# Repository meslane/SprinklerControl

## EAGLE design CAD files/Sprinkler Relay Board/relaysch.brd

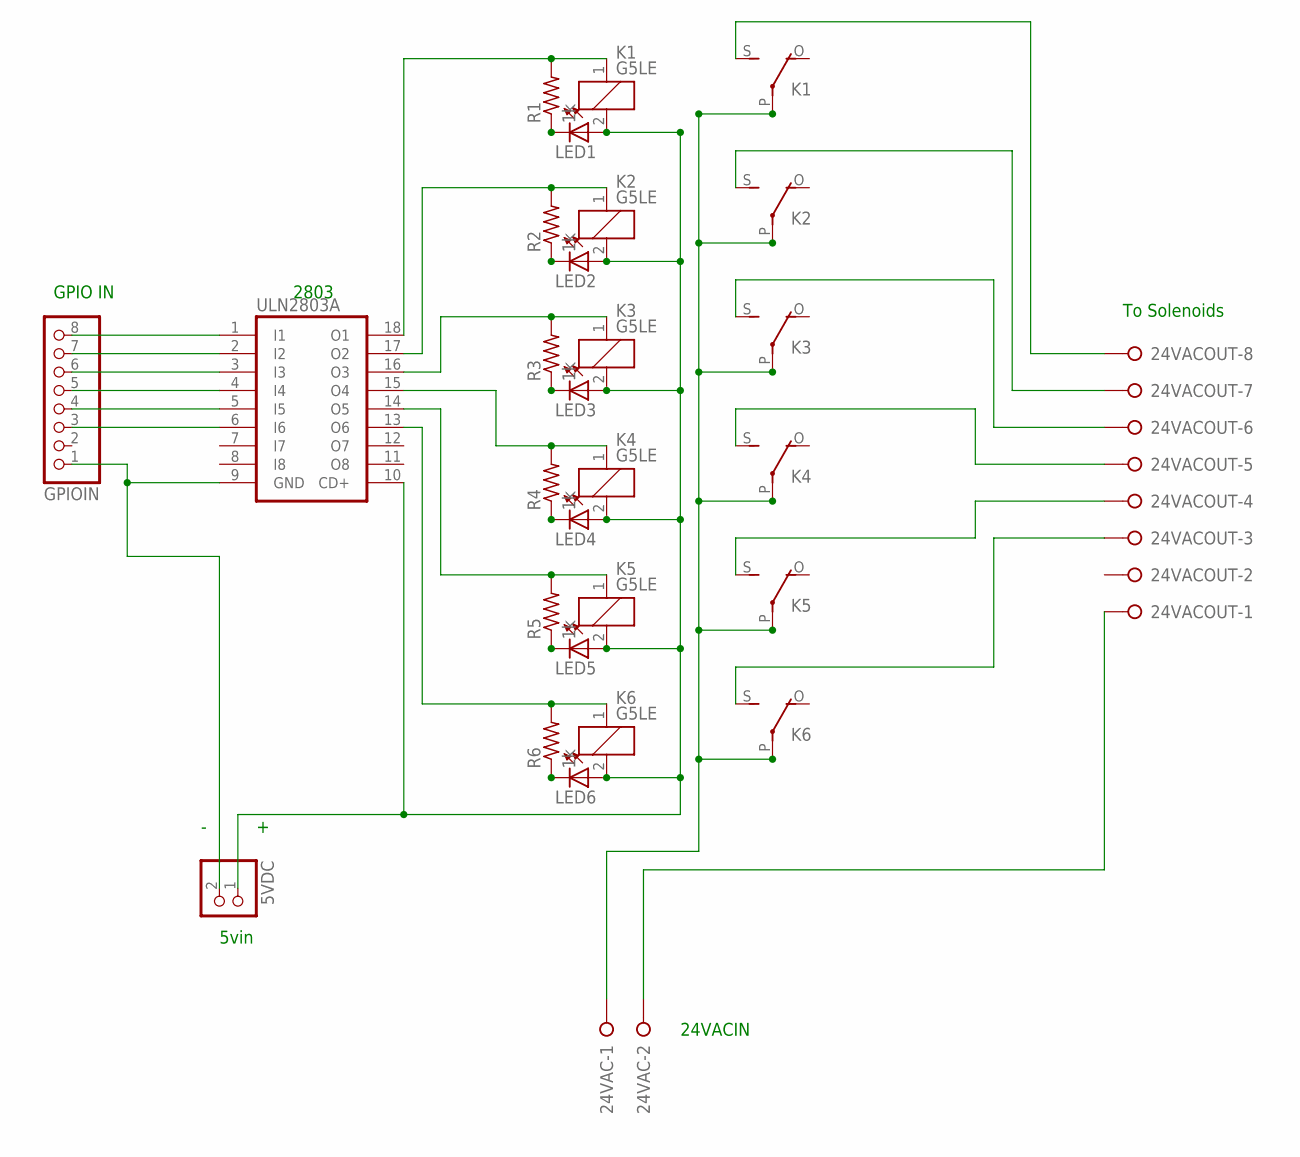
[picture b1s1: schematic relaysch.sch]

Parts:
5VDC: PINHD-1X2; 1X02
24VAC: W237-02P; W237-132
24VACOUT: W237-08P; W237-8P
GPIOIN: PINHD-1X8BIG; 1X08-BIG
K1, K2, K3, K4, K5, K6: G5LE
LED1, LED2, LED3, LED4, LED5, LED6: LED5MM
R1, R2, R3, R4, R5, R6: 1k; 0805-THM
ULN2803A: ULN2803A; DIL18

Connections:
5VIN: 5VDC.1, K1.2, K2.2, K3.2, K4.2, K5.2, K6.2, LED1.A, LED2.A, LED3.A, LED4.A, LED5.A, LED6.A, ULN2803A.10 (CD+)
unnamed: 24VACOUT.8, K1.S
unnamed: 24VACOUT.7, K2.S
unnamed: 24VACOUT.6, K3.S
unnamed: 24VACOUT.5, K4.S
unnamed: 24VACOUT.4, K5.S
unnamed: 24VACOUT.3, K6.S
unnamed: 24VAC.1, K1.P, K2.P, K3.P, K4.P, K5.P, K6.P
unnamed: K1.1, R1.2, ULN2803A.18 (O1)
unnamed: LED6.K (C), R6.1
unnamed: 24VAC.2, 24VACOUT.1
unnamed: K3.1, R3.2, ULN2803A.16 (O3)
unnamed: K4.1, R4.2, ULN2803A.15 (O4)
unnamed: K5.1, R5.2, ULN2803A.14 (O5)
unnamed: K6.1, R6.2, ULN2803A.13 (O6)
unnamed: LED1.K (C), R1.1
unnamed: LED2.K (C), R2.1
unnamed: LED3.K (C), R3.1
unnamed: LED5.K (C), R5.1
unnamed: LED4.K (C), R4.1
unnamed: K2.1, R2.2, ULN2803A.17 (O2)
unnamed: 5VDC.2, GPIOIN.1, ULN2803A.9 (GND)
unnamed: GPIOIN.8, ULN2803A.1 (I1)
unnamed: GPIOIN.7, ULN2803A.2 (I2)
unnamed: GPIOIN.6, ULN2803A.3 (I3)
unnamed: GPIOIN.5, ULN2803A.4 (I4)
unnamed: GPIOIN.4, ULN2803A.5 (I5)
unnamed: GPIOIN.3, ULN2803A.6 (I6)

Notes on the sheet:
5vin
24VACIN
GPIO IN
2803
To Solenoids

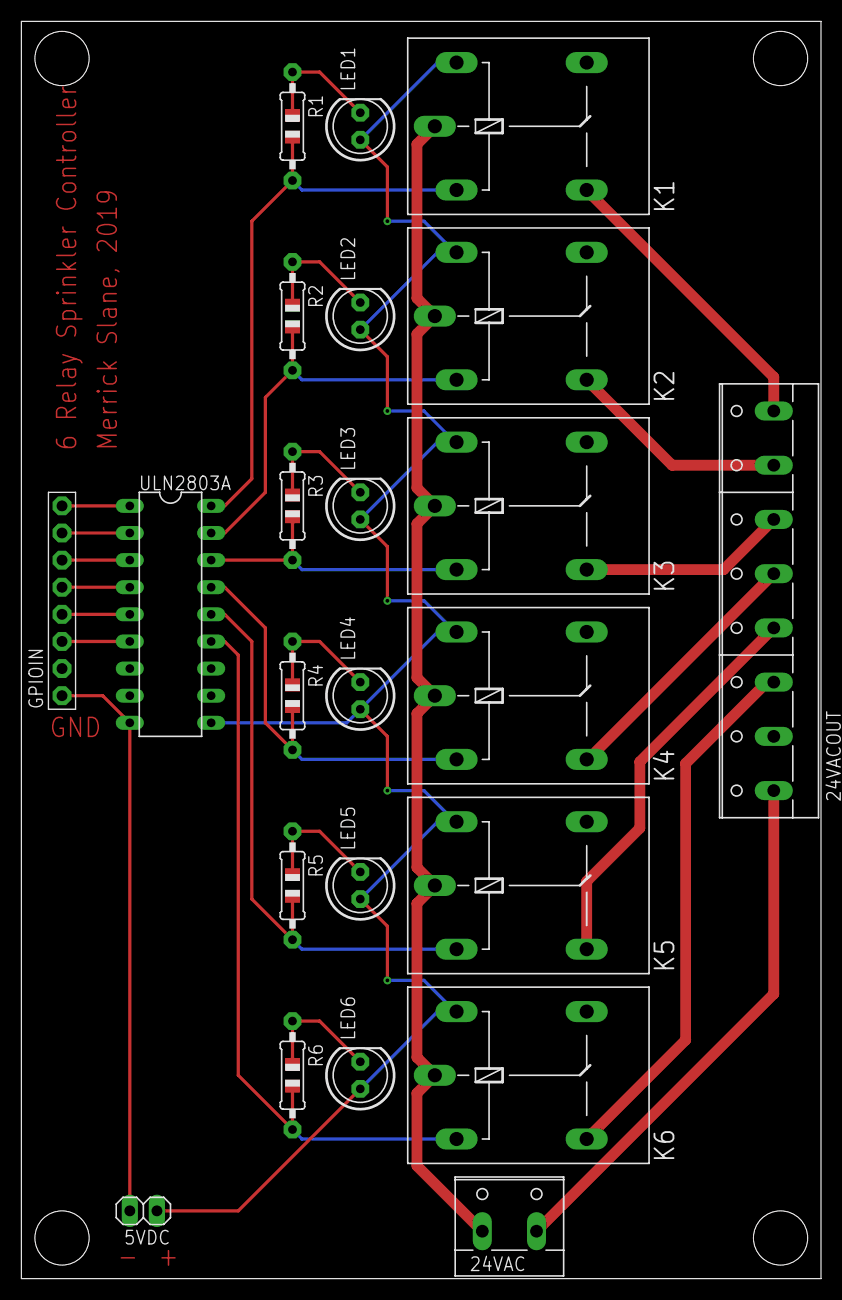
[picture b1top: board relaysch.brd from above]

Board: 2 copper layers, 74.9 x 117.8 mm, 23 parts (0 on the bottom side), 28 nets.

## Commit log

2019-09-13 updated valve code and added CAD files for relay board
2019-09-17 updated .json file and some other things
2019-09-17 added GPIO code
2019-09-17 tested on actual pi hardware and updated GPIO code
2019-09-18 added manual valve toggles
2019-09-19 fixed manual valve toggle code
2019-09-19 uncommented GPIO code
